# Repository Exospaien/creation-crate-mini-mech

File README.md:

# creation-crate-mini-mech

Contains Arduino sketches and pcb designs for the electrical systems of the mini mech project.

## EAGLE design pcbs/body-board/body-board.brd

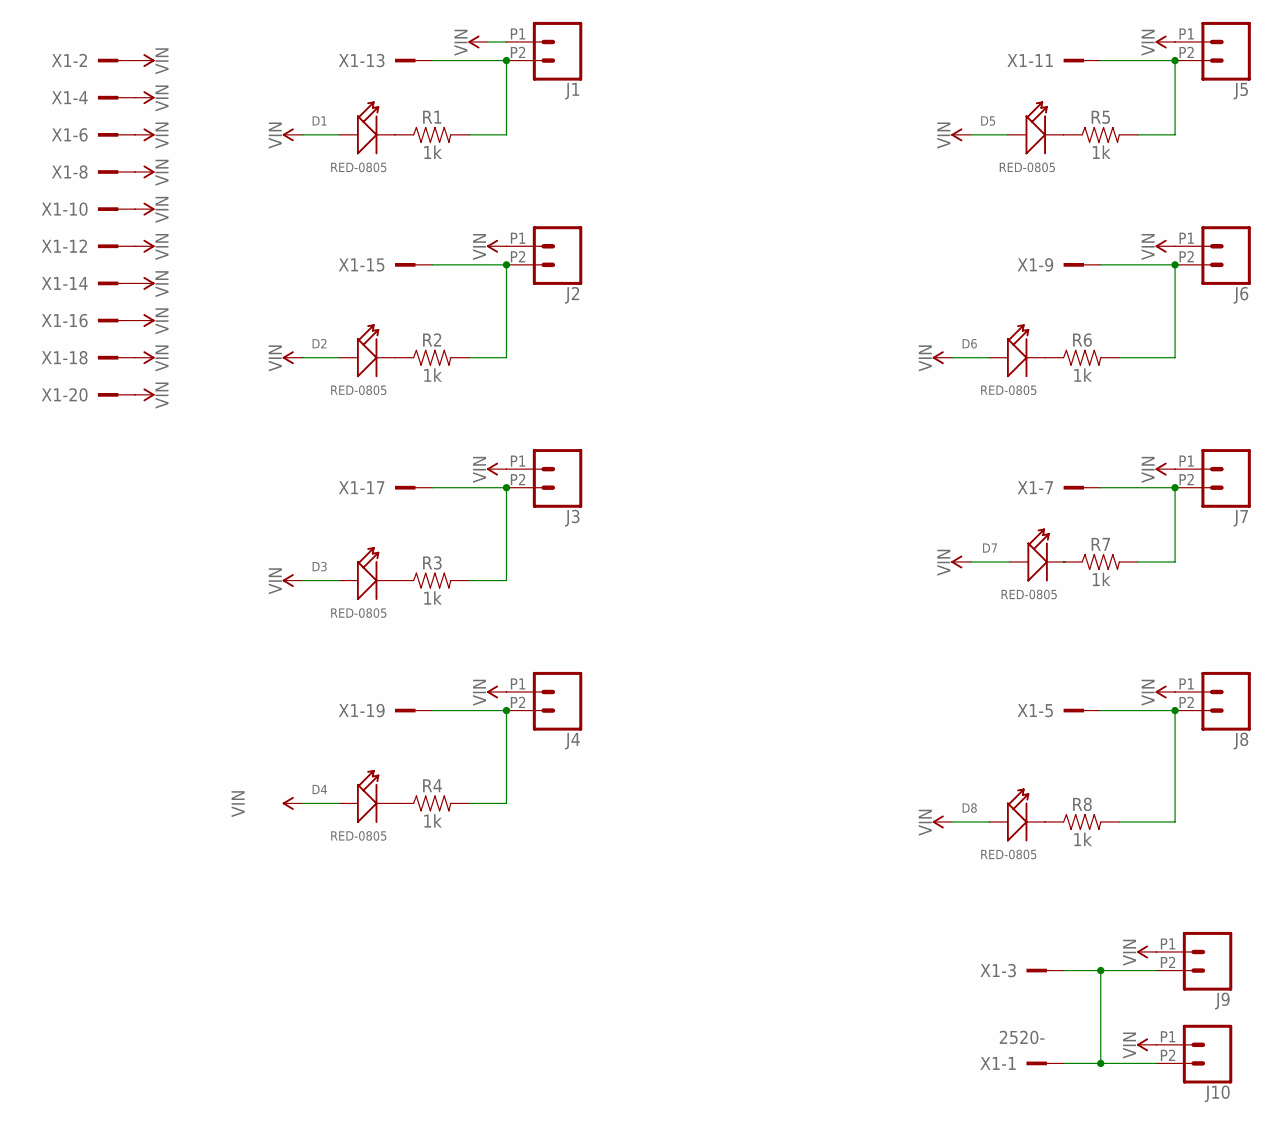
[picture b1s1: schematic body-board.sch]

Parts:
D1, D2, D3, D4, D5, D6, D7, D8: RED-0805; LED-0805
J1, J2, J3, J4, J5, J6, J7, J8, J9, J10: CONN_022.54MM_SCREWTERM; 1X02_2.54_SCREWTERM
R1, R2, R3, R4, R5, R6, R7, R8: 1k; 0603
X1: 2520-; PAK100/2500-20

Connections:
unnamed: D1.-, R1.1
unnamed: D2.-, R2.1
unnamed: D3.-, R3.1
unnamed: D4.-, R4.1
unnamed: D6.-, R6.1
unnamed: D8.-, R8.1
unnamed: J9.P2 (2), J10.P2 (2), X1.1, X1.3
unnamed: J8.P2 (2), R8.2, X1.5
unnamed: J7.P2 (2), R7.2, X1.7
unnamed: J6.P2 (2), R6.2, X1.9
unnamed: J5.P2 (2), R5.2, X1.11
unnamed: J1.P2 (2), R1.2, X1.13
unnamed: J2.P2 (2), R2.2, X1.15
unnamed: J3.P2 (2), R3.2, X1.17
unnamed: J4.P2 (2), R4.2, X1.19
unnamed: D7.-, R7.1
unnamed: D5.-, R5.1
VIN: D1.+, D2.+, D3.+, D4.+, D5.+, D6.+, D7.+, D8.+, J1.P1 (1), J2.P1 (1), J3.P1 (1), J4.P1 (1), J5.P1 (1), J6.P1 (1), J7.P1 (1), J8.P1 (1), J9.P1 (1), J10.P1 (1), X1.2, X1.4, X1.6, X1.8, X1.10, X1.12, X1.14, X1.16, X1.18, X1.20

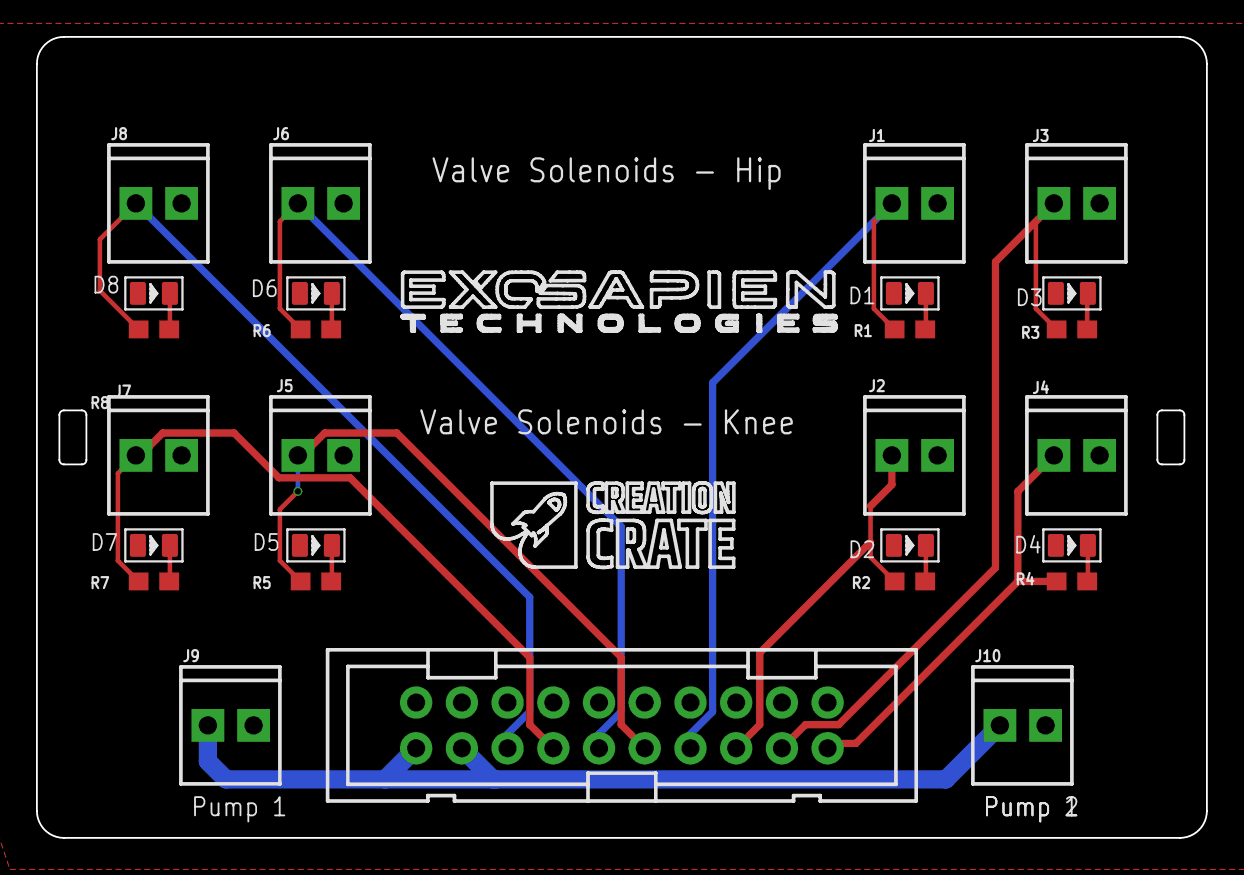
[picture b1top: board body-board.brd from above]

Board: 2 copper layers, 65.0 x 44.5 mm, 27 parts (0 on the bottom side), 18 nets.

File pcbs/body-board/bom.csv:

"Qty";"Value";"Device";"Package";"Parts";"Description";"MF";"MPN";"OC_FARNELL";"OC_NEWARK";"POPULARITY";"PROD_ID";"VALUE";
"10";"";"CONN_022.54MM_SCREWTERM";"1X02_2.54_SCREWTERM";"J1, J2, J3, J4, J5, J6, J7, J8, J9, J10";"Multi connection point. Often used as Generic Header-pin footprint for 0.1 inch spaced/style header connections";"";"";"";"";"";"";"";
"9";"1k";"1KOHM-0603-1/10W-1%";"0603";"R1, R2, R3, R4, R5, R6, R7, R8, R9";"1kΩ resistor";"";"";"";"";"";"RES-07856";"1k";
"1";"2520-";"2520-";"PAK100/2500-20";"X1";"3M (TM) Pak 100 4-Wall Header";"";"";"unknown";"unknown";"0";"";"";
"9";"RED-0805";"SMD-LED-CLEAR-RED(0805)";"LED-0805";"D1, D2, D3, D4, D5, D6, D7, D8, D9";"304090046";"";"17-215SURC/S530-A2/TR8";"";"";"";"";"RED-0805";

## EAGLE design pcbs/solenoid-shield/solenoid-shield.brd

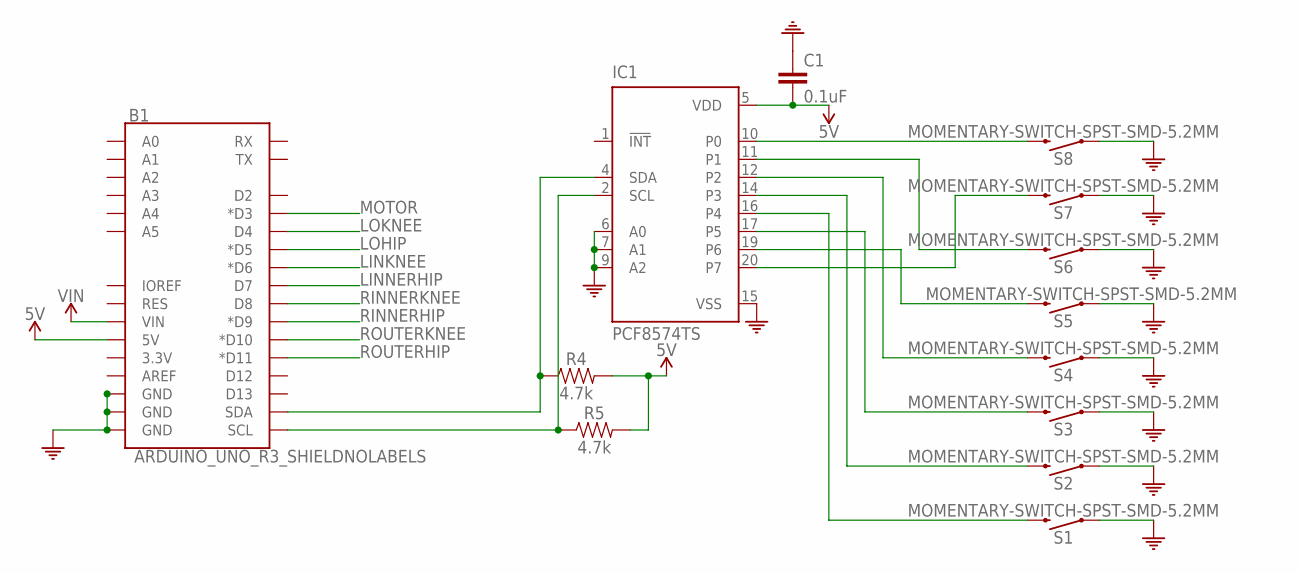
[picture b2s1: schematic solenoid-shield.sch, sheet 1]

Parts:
B1: ARDUINO_UNO_R3_SHIELDNOLABELS; UNO_R3_SHIELD_NOLABELS
C1: 0.1uF; 0603
IC1: PCF8574TS; SSOP20
R4, R5: 4.7k; 0603
S1, S2, S3, S4, S5, S6, S7, S8: MOMENTARY-SWITCH-SPST-SMD-5.2MM; TACTILE_SWITCH_SMD_5.2MM

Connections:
5V: B1.5V, C1.2, IC1.5 (VDD), R4.2, R5.2
COM: B1.GND@0 (GND), B1.GND@1 (GND), B1.GND@2 (GND), C1.1, IC1.6 (A0), IC1.7 (A1), IC1.9 (A2), IC1.15 (VSS), S1.1, S2.1, S3.1, S4.1, S5.1, S6.1, S7.1, S8.1; also elsewhere on the board
LINKNEE: B1.D6 (*D6); also elsewhere on the board
LINNERHIP: B1.D7; also elsewhere on the board
LOHIP: B1.D5 (*D5); also elsewhere on the board
LOKNEE: B1.D4; also elsewhere on the board
MOTOR: B1.D3 (*D3); also elsewhere on the board
unnamed: IC1.10 (P0), S8.3 (2)
unnamed: IC1.20 (P7), S7.3 (2)
unnamed: B1.SDA, IC1.4 (SDA), R4.1
unnamed: IC1.11 (P1), S6.3 (2)
unnamed: IC1.19 (P6), S5.3 (2)
unnamed: IC1.12 (P2), S4.3 (2)
unnamed: IC1.17 (P5), S3.3 (2)
unnamed: IC1.14 (P3), S2.3 (2)
unnamed: IC1.16 (P4), S1.3 (2)
unnamed: B1.SCL, IC1.2 (SCL), R5.1
RINNERHIP: B1.D9 (*D9); also elsewhere on the board
RINNERKNEE: B1.D8; also elsewhere on the board
ROUTERHIP: B1.D11 (*D11); also elsewhere on the board
ROUTERKNEE: B1.D10 (*D10); also elsewhere on the board
VIN: B1.VIN; also elsewhere on the board

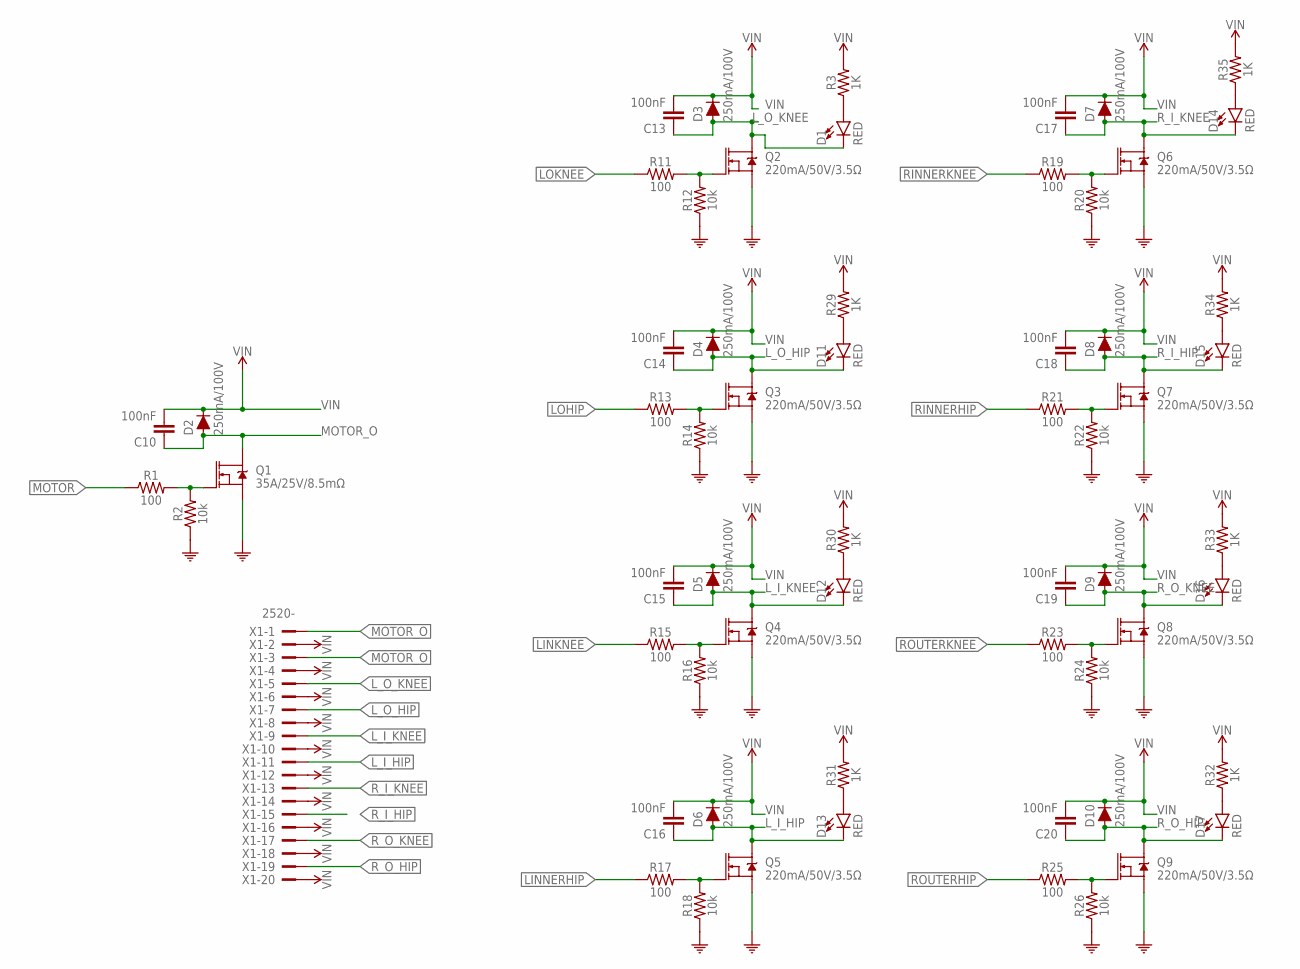
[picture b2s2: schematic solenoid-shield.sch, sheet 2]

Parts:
C10, C13, C14, C15, C16, C17, C18, C19, C20: 100nF; C0603-ROUND
D1, D11, D12, D13, D14, D15, D16, D17: RED; LED-0603
D2, D3, D4, D5, D6, D7, D8, D9, D10: 250mA/100V; SOD-323
Q1: 35A/25V/8.5mΩ; DPAK
Q2, Q3, Q4, Q5, Q6, Q7, Q8, Q9: 220mA/50V/3.5Ω; SOT23-3
R1, R11, R13, R15, R17, R19, R21, R23, R25: 100; 0603
R2, R12, R14, R16, R18, R20, R22, R24, R26: 10k; 0603
R3, R29, R30, R31, R32, R33, R34, R35: 1K; 0603
X1: 2520-; PAK100/2500-20

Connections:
COM: Q1.3 (S), Q2.2 (S), Q3.2 (S), Q4.2 (S), Q5.2 (S), Q6.2 (S), Q7.2 (S), Q8.2 (S), Q9.2 (S), R2.1, R12.1, R14.1, R16.1, R18.1, R20.1, R22.1, R24.1, R26.1; also elsewhere on the board
LINKNEE: R15.1; also elsewhere on the board
LINNERHIP: R17.1; also elsewhere on the board
LOHIP: R13.1; also elsewhere on the board
LOKNEE: R11.1; also elsewhere on the board
L_I_HIP: C16.1, D6.A, D13.C, Q5.3 (D), X1.11
L_I_KNEE: C15.1, D5.A, D12.C, Q4.3 (D), X1.9
L_O_HIP: C14.1, D4.A, D11.C, Q3.3 (D), X1.7
L_O_KNEE: C13.1, D1.C, D3.A, Q2.3 (D), X1.5
MOTOR: R1.1; also elsewhere on the board
MOTOR_O: C10.1, D2.A, Q1.4 (D), X1.1, X1.3
unnamed: D1.A, R3.1
unnamed: D11.A, R29.1
unnamed: D12.A, R30.1
unnamed: D13.A, R31.1
unnamed: D17.A, R32.1
unnamed: D16.A, R33.1
unnamed: D15.A, R34.1
unnamed: D14.A, R35.1
unnamed: Q1.1 (G), R1.2, R2.2
unnamed: Q2.1 (G), R11.2, R12.2
unnamed: Q3.1 (G), R13.2, R14.2
unnamed: Q4.1 (G), R15.2, R16.2
unnamed: Q5.1 (G), R17.2, R18.2
unnamed: Q6.1 (G), R19.2, R20.2
unnamed: Q7.1 (G), R21.2, R22.2
unnamed: Q8.1 (G), R23.2, R24.2
unnamed: Q9.1 (G), R25.2, R26.2
RINNERHIP: R21.1; also elsewhere on the board
RINNERKNEE: R19.1; also elsewhere on the board
ROUTERHIP: R25.1; also elsewhere on the board
ROUTERKNEE: R23.1; also elsewhere on the board
R_I_HIP: C18.1, D8.A, D15.C, Q7.3 (D), X1.15
R_I_KNEE: C17.1, D7.A, D14.C, Q6.3 (D), X1.13
R_O_HIP: C20.1, D10.A, D17.C, Q9.3 (D), X1.19
R_O_KNEE: C19.1, D9.A, D16.C, Q8.3 (D), X1.17
VIN: C10.2, C13.2, C14.2, C15.2, C16.2, C17.2, C18.2, C19.2, C20.2, D2.C, D3.C, D4.C, D5.C, D6.C, D7.C, D8.C, D9.C, D10.C, R3.2, R29.2, R30.2, R31.2, R32.2, R33.2, R34.2, R35.2, X1.2, X1.4, X1.6, X1.8, X1.10, X1.12, X1.14, X1.16, X1.18, X1.20; also elsewhere on the board

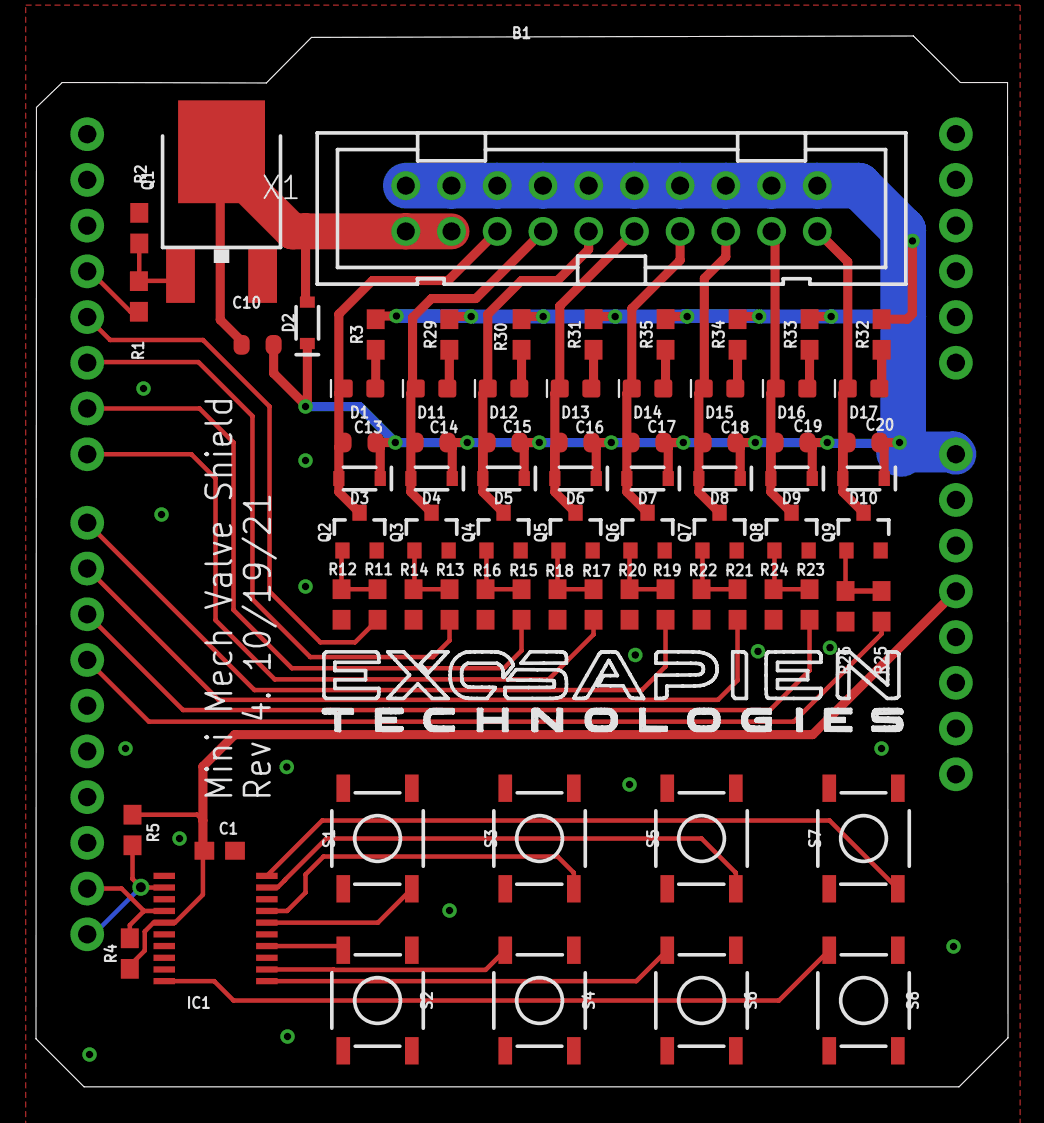
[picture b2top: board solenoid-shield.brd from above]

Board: 2 copper layers, 54.0 x 58.4 mm, 75 parts (0 on the bottom side), 48 nets.

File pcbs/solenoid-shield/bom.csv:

"Qty";"Value";"Device";"Package";"Parts";"Description";"CASE";"MF";"MONTHLY_USAGE";"MPN";"OC_FARNELL";"OC_NEWARK";"PART_NUMBER";"POPULARITY";"PRICE";"PROD_ID";"SF_SKU";"SUPPLIER";"TYPE";"VALUE";
"1";"0.1uF";"0.1UF-0603-25V-5%";"0603";"C1";"0.1µF ceramic capacitors";"";"";"";"";"";"";"";"";"";"CAP-08604";"";"";"";"0.1uF";
"9";"100";"100OHM-0603-1/10W-1%";"0603";"R1, R11, R13, R15, R17, R19, R21, R23, R25";"100Ω resistor";"";"";"";"";"";"";"";"";"";"RES-07863";"";"";"";"100";
"9";"100nF";"0015_100NF_0603";"C0603-ROUND";"C10, C13, C14, C15, C16, C17, C18, C19, C20";"100nF 0603 50V";"0603";"";"_____";"";"";"";"cl10b104kbnc";"";"_____";"";"";"_____";"Condensatori";"100nF";
"9";"10k";"10KOHM-0603-1/10W-1%";"0603";"R2, R12, R14, R16, R18, R20, R22, R24, R26";"10kΩ resistor";"";"";"";"";"";"";"";"";"";"RES-00824";"";"";"";"10k";
"8";"1K";"10KOHM-0603-1/10W-1%";"0603";"R3, R29, R30, R31, R32, R33, R34, R35";"10kΩ resistor";"";"";"";"";"";"";"";"";"";"RES-00824";"";"";"";"10k";
"8";"220mA/50V/3.5Ω";"MOSFET-NCH-BSS138";"SOT23-3";"Q2, Q3, Q4, Q5, Q6, Q7, Q8, Q9";"N-channel MOSFETs";"";"";"";"";"";"";"";"";"";"TRANS-00830";"";"";"";"220mA/50V/3.5Ω";
"9";"250mA/100V";"DIODE-BAS16J";"SOD-323";"D2, D3, D4, D5, D6, D7, D8, D9, D10";"Diode";"";"";"";"";"";"";"";"";"";"DIO-09646";"";"";"";"250mA/100V";
"1";"2520-";"2520-";"PAK100/2500-20";"X1";"3M (TM) Pak 100 4-Wall Header";"";"";"";"";"unknown";"unknown";"";"0";"";"";"";"";"";"";
"1";"35A/25V/8.5mΩ";"MOSFET-NCH-FDD8780";"DPAK";"Q1";"N-channel MOSFETs";"";"";"";"";"";"";"";"";"";"TRANS-09984";"";"";"";"35A/25V/8.5mΩ";
"2";"4.7k";"4.7KOHM-0603-1/10W-1%";"0603";"R4, R5";"4.7kΩ resistor";"";"";"";"";"";"";"";"";"";"RES-07857";"";"";"";"4.7k";
"1";"ARDUINO_UNO_R3_SHIELDNOLABELS";"ARDUINO_UNO_R3_SHIELDNOLABELS";"UNO_R3_SHIELD_NOLABELS";"B1";"Arduino R3 Shield Footprint";"";"";"";"";"";"";"";"";"";"";"";"";"";"";
"8";"MOMENTARY-SWITCH-SPST-SMD-5.2MM";"MOMENTARY-SWITCH-SPST-SMD-5.2MM";"TACTILE_SWITCH_SMD_5.2MM";"S1, S2, S3, S4, S5, S6, S7, S8";"Momentary Switch (Pushbutton) - SPST";"";"";"";"";"";"";"";"";"";"SWCH-08247";"COM-08720";"";"";"";
"1";"PCF8574TS";"PCF8574TS";"SSOP20";"IC1";"I2C-Bus Remote 8-bit I/O expander";"";"";"";"PCF8574TS/3,118";"1506644";"70R6873";"";"0";"";"";"";"";"";"";
"8";"RED";"LED-RED0603";"LED-0603";"D1, D11, D12, D13, D14, D15, D16, D17";"Red SMD LED";"";"";"";"";"";"";"";"";"";"DIO-00819";"";"";"";"RED";

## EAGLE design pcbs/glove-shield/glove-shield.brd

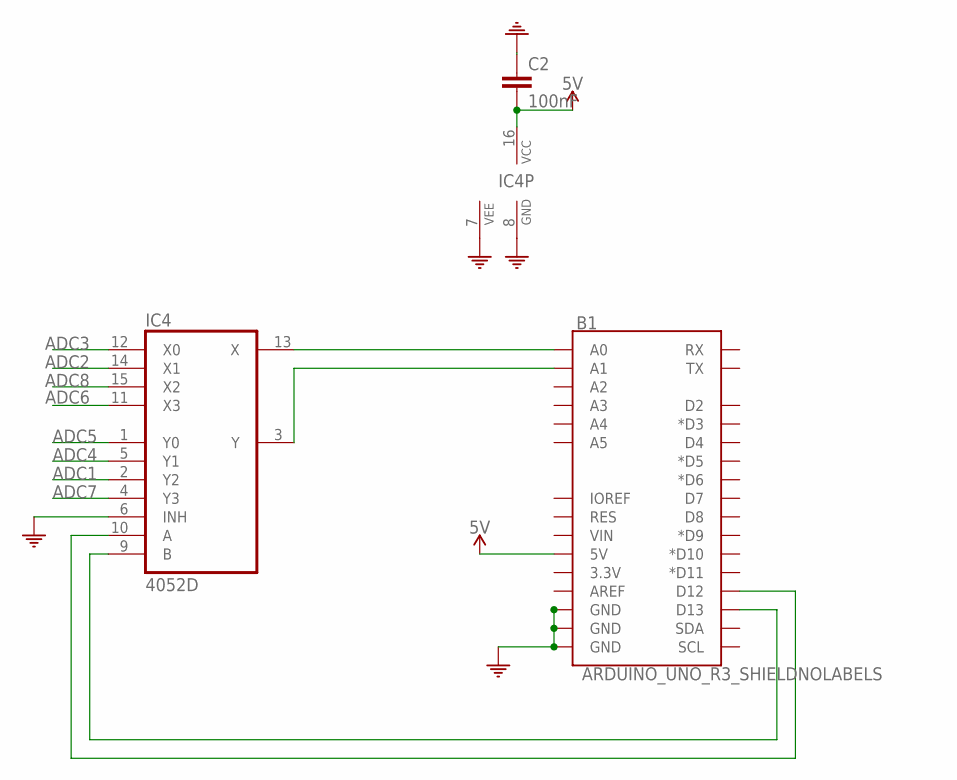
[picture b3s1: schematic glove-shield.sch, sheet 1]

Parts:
B1: ARDUINO_UNO_R3_SHIELDNOLABELS; UNO_R3_SHIELD_NOLABELS
C2: 100nF; C0603-ROUND
IC4: 4052D; SO16

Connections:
5V: B1.5V, C2.2, IC4.16 (VCC); also elsewhere on the board
ADC1: IC4.2 (Y2); also elsewhere on the board
ADC2: IC4.14 (X1); also elsewhere on the board
ADC3: IC4.12 (X0); also elsewhere on the board
ADC4: IC4.5 (Y1); also elsewhere on the board
ADC5: IC4.1 (Y0); also elsewhere on the board
ADC6: IC4.11 (X3); also elsewhere on the board
ADC7: IC4.4 (Y3); also elsewhere on the board
ADC8: IC4.15 (X2); also elsewhere on the board
COM: B1.GND@0 (GND), B1.GND@1 (GND), B1.GND@2 (GND), C2.1, IC4.6 (INH), IC4.7 (VEE), IC4.8 (GND); also elsewhere on the board
unnamed: B1.D13, IC4.9 (B)
unnamed: B1.A0, IC4.13 (X)
unnamed: B1.A1, IC4.3 (Y)
unnamed: B1.D12, IC4.10 (A)

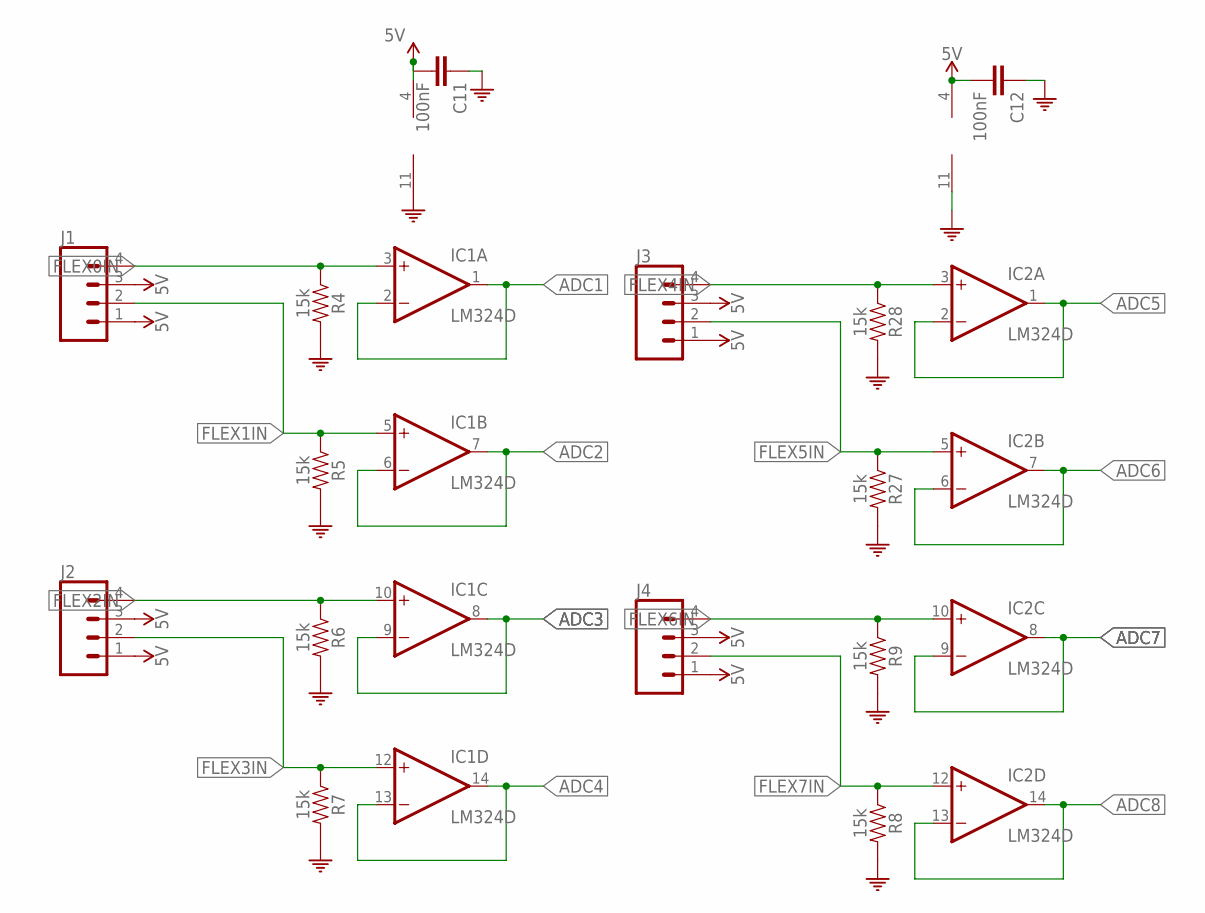
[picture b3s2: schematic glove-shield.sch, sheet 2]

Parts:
C11, C12: 100nF; C0603-ROUND
IC1, IC2: LM324D; SO14
J1, J2, J3, J4: CONN_04JST-PTH; JST-4-PTH
R4, R5, R6, R7, R8, R9, R27, R28: 15k; 0603

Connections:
5V: C11.2, C12.2, IC1.4 (V+), IC2.4 (V+), J1.1, J1.3, J2.1, J2.3, J3.1, J3.3, J4.1, J4.3; also elsewhere on the board
ADC1: IC1.1 (OUT), IC1.2 (-IN); also elsewhere on the board
ADC2: IC1.6 (-IN), IC1.7 (OUT); also elsewhere on the board
ADC3: IC1.8 (OUT), IC1.9 (-IN); also elsewhere on the board
ADC4: IC1.13 (-IN), IC1.14 (OUT); also elsewhere on the board
ADC5: IC2.1 (OUT), IC2.2 (-IN); also elsewhere on the board
ADC6: IC2.6 (-IN), IC2.7 (OUT); also elsewhere on the board
ADC7: IC2.8 (OUT), IC2.9 (-IN); also elsewhere on the board
ADC8: IC2.13 (-IN), IC2.14 (OUT); also elsewhere on the board
COM: C11.1, C12.1, IC1.11 (V-), IC2.11 (V-), R4.2, R5.2, R6.2, R7.2, R8.2, R9.2, R27.2, R28.2; also elsewhere on the board
FLEX0IN: IC1.3 (+IN), J1.4, R4.1
FLEX1IN: IC1.5 (+IN), J1.2, R5.1
FLEX2IN: IC1.10 (+IN), J2.4, R6.1
FLEX3IN: IC1.12 (+IN), J2.2, R7.1
FLEX4IN: IC2.3 (+IN), J3.4, R28.1
FLEX5IN: IC2.5 (+IN), J3.2, R27.1
FLEX6IN: IC2.10 (+IN), J4.4, R9.1
FLEX7IN: IC2.12 (+IN), J4.2, R8.1

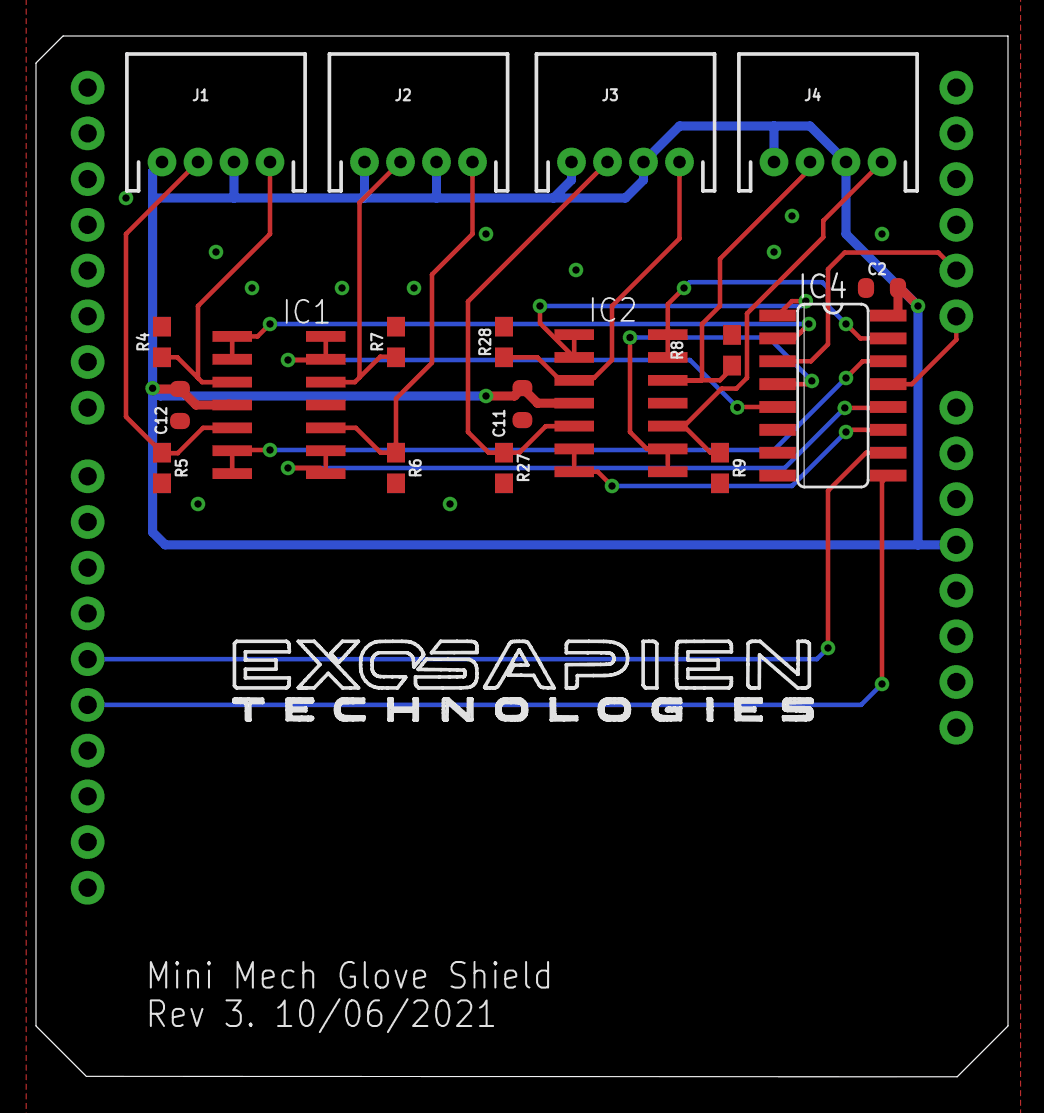
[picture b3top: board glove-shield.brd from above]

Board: 2 copper layers, 54.0 x 57.8 mm, 19 parts (0 on the bottom side), 22 nets.

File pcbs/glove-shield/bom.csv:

"Qty";"Value";"Device";"Package";"Parts";"Description";"CASE";"MONTHLY_USAGE";"PART_NUMBER";"POPULARITY";"PRICE";"PROD_ID";"SF_ID";"SUPPLIER";"TYPE";"VALUE";
"4";"";"CONN_04JST-PTH";"JST-4-PTH";"J1, J2, J3, J4";"Multi connection point. Often used as Generic Header-pin footprint for 0.1 inch spaced/style header connections";"";"";"";"";"";"WIRE-13531";"PRT-09916";"";"";"";
"3";"100nF";"0015_100NF_0603";"C0603-ROUND";"C2, C11, C12";"100nF 0603 50V";"0603";"_____";"cl10b104kbnc";"";"_____";"";"";"_____";"Condensatori";"100nF";
"8";"15k";"RESISTOR0603";"0603";"R4, R5, R6, R7, R8, R9, R27, R28";"Generic Resistor Package";"";"";"";"";"";" ";"";"";"";" ";
"1";"4052D";"4052D";"SO16";"IC4";"Dual 4-channel ANALOG MULTIPLEXER";"";"";"";"1";"";"";"";"";"";"";
"1";"ARDUINO_UNO_R3_SHIELDNOLABELS";"ARDUINO_UNO_R3_SHIELDNOLABELS";"UNO_R3_SHIELD_NOLABELS";"B1";"Arduino R3 Shield Footprint";"";"";"";"";"";"";"";"";"";"";
"2";"LM324D";"LM324D";"SO14";"IC1, IC2";"OP AMP";"";"";"";"1";"";"";"";"";"";"";

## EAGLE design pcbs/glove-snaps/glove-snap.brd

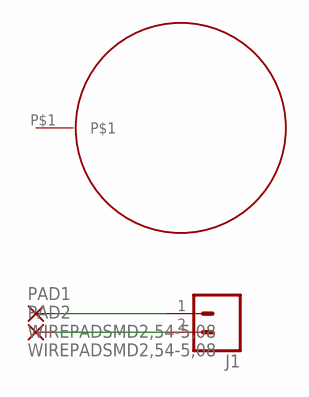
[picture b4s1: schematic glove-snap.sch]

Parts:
J1: CONN_02LOCK_LONGPADS; 1X02_LOCK_LONGPADS
PAD1, PAD2: WIREPADSMD2,54-5,08; SMD2,54-5,08
U$1: SNAP

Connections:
unnamed: J1.1, PAD1.1
unnamed: J1.2, PAD2.1

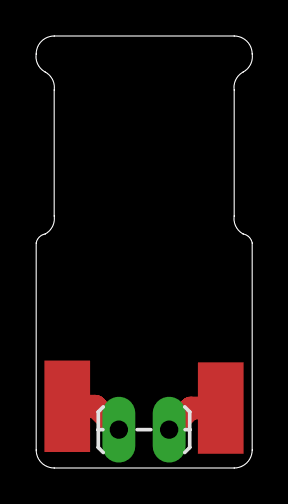
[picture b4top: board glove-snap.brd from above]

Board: 2 copper layers, 12.0 x 24.0 mm, 4 parts (1 on the bottom side), 2 nets.

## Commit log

2021-08-03 Add serial control sketch
2021-08-04 Latest glove code. Untested
2021-08-09 Fix static issues
2021-08-12 Add button control
2021-08-12 support for glove
2021-08-16 Update sketches
2021-08-18 Latest work
2021-08-18 Update bom and exported schematics
2021-08-18 Update pcb images
2021-08-21 Update button sketch based on Curtis' feedback
2021-10-06 Update glove control code
2021-10-06 Updated glove shield pcb design
2021-10-20 Update boards to latest
2021-10-21 Updated boards to latest, updated bom export, and CAM exports
2021-10-24 Updated calibrations
2021-10-26 calibrated sensors
2021-11-22 Update to latest version with glove control
2021-11-22 Update mapping of glove
2022-01-23 Updated body board sans creation crate logo
2022-01-23 Update based on feedback
2022-01-23 Zipped gerbers for latest board rev
2022-01-23 silkscreen fix
2022-01-23 change zip tie position
2022-02-08 Update code with comments and remove unuused method

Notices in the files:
parts and their libraries:
SparkFun-Connectors: Licensing: Creative Commons ShareAlike 4.0 International - https://creativecommons.org/licenses/by-sa/4.0
